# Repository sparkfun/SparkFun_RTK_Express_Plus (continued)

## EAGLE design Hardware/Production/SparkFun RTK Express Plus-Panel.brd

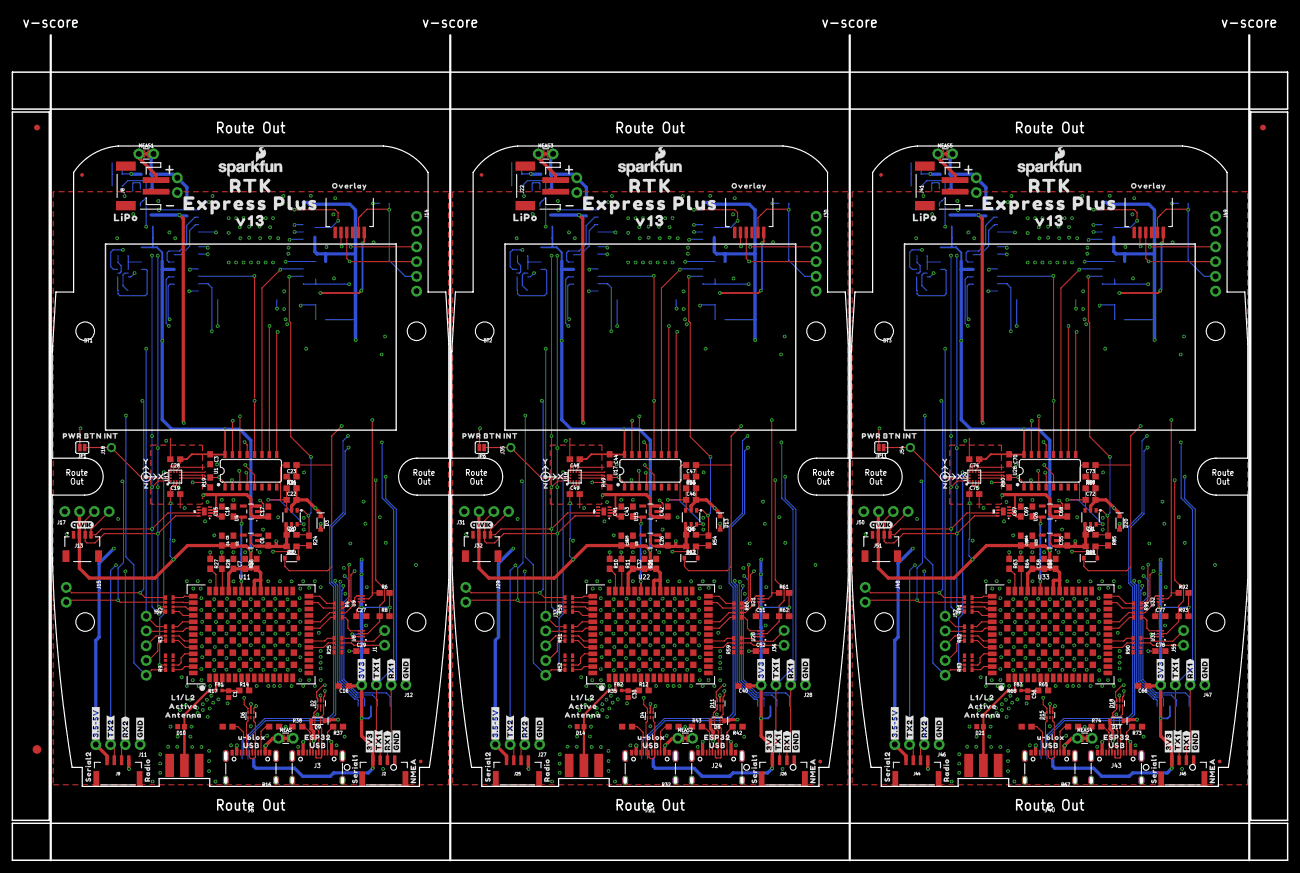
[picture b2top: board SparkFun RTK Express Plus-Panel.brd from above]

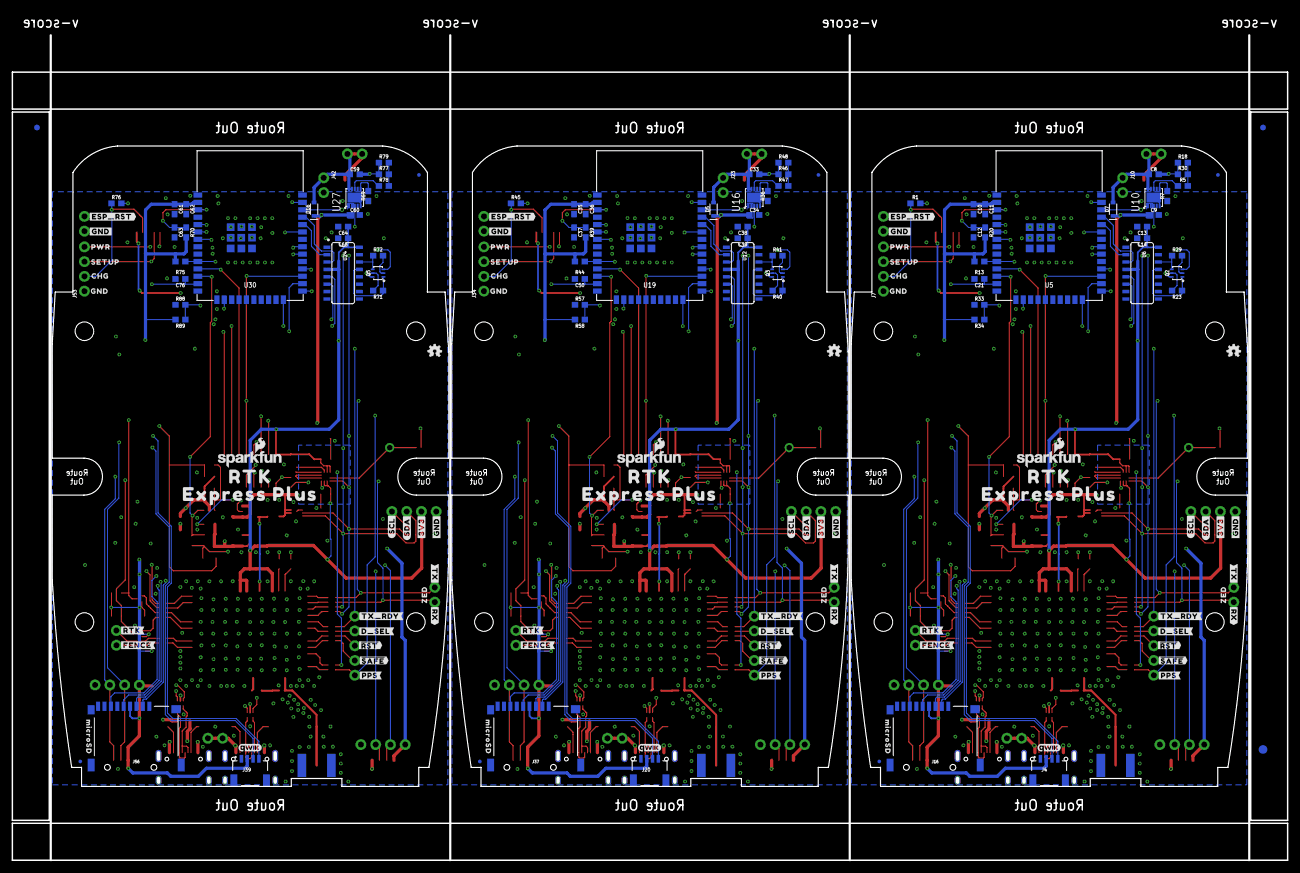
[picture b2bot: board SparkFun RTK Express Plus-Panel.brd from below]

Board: 4 copper layers, 219.3 x 141.9 mm, 510 parts (171 on the bottom side), 276 nets.

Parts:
BT1, BT2, BT3: LIPO-OUTLINE1000; LIPO-1000
C1, C30, C56: 47pF; 0402
C2, C4, C6, C17, C18, C24, C26, C31, C42, C43, C53, C55, C57, C68, C69: 1.0uF; 0603
C3, C5, C7, C11, C12, C13, C15, C16, C21, C22, C23, C25, C27, C28, C29, C32, C36, C37, C38, C40, C41, C44, C46, C47, C48, C50, C51, C52, C54, C58, C62, C63, C64, C66, C67, C70, C72, C73, C74, C76, C77, C78: 0.1uF; 0603
C8, C9, C33, C34, C59, C60: 4.7uF; 0603
C10, C14, C19, C20, C35, C39, C45, C49, C61, C65, C71, C75: 10uF; 0603
D1, D12, D19: 250mA/100V; SOD-323
D2, D4, D6, D11, D15, D18: PRTR5V0U2F; SOT886
D3, D5, D7, D8, D9, D13, D16, D17, D20: 3A/10V/280mV; SOD-323
D10, D14, D21: PESD0402-0402; 0402
E1, E2, E3: SMA; SMA-EDGE
E$1, E$2, E$3, E$4: FIDUCIAL-1X2
E$5, E$6: FIDUCIAL-1.5X3
FB1, FB2, FB3: 2.66Ω; 0402-TIGHT
J1, J10, J14, J15, J23, J29, J30, J36, J42, J48, J49, J55: 1X02_NO_SILK
J2, J9, J25, J26, J44, J45: JST-4-SMD-1.25MM-LOCKING
J3, J5, J21, J24, J40, J43: USB Female Type C Connector; USB-C-16P_4LAYER-PADS
J4, J20, J39: External; JST04_1MM_RA
J6, J33, J52: 1X05_NO_SILK
J7, J11, J12, J27, J28, J34, J46, J47, J53: 1X04_NO_SILK
J8, J22, J41: JST-2-SMD
J13, J32, J51: Internal; JST04_1MM_RA
J16, J37, J56: MICRO-SD-PUSH-PUSH-EXT-PIN; MICROSD-EXTERNALPIN
J17, J31, J50: Qwiic Right Angle; 1X04_NO_SILK
J18, J35, J54: 1X01_NO_SILK
J19, J38, J57: FPC_6_1MM-LIF
JP1, JP6, JP11: JUMPER-SMT_2_NO_SILK; SMT-JUMPER_2_NO_SILK
JP2, JP3, JP4, JP5, JP7, JP8, JP9, JP10, JP21, JP61, JP71, JP81: FIDUCIALUFIDUCIAL; FIDUCIAL-MICRO
LOGO1, LOGO4, LOGO7: OSHW-LOGOMINI; OSHW-LOGO-MINI
LOGO2, LOGO3, LOGO5, LOGO6, LOGO8, LOGO9: SFE_LOGO_NAME_FLAME.1_INCH; SFE_LOGO_NAME_FLAME_.1
MEAS, MEAS1, MEAS2, MEAS3, MEAS4, MEAS5: JUMPER-COMBO_2_NC_TRACE; COMBO-JUMPER_2_NC_TRACE
Q1, Q4, Q6: SIL2308-TP; SOT26
Q2, Q3, Q5: MBT3904DW1T1; SC70-6
R1, R45, R76: 470; 0603
R2, R3, R4, R9, R25, R50, R51, R52, R59, R60, R81, R82, R83, R90, R91: 33; 1206_RA
R5, R47, R78: 0; 0603
R6, R8, R18, R23, R29, R31, R33, R40, R41, R48, R56, R57, R61, R62, R71, R72, R79, R87, R88, R92, R93: 10k; 0603
R7, R19, R36, R49, R69, R80: 1k; 0603
R10, R11, R27, R28, R63, R64: 27; 0603
R12, R14, R65: 10; 0603
R13, R15, R20, R21, R22, R26, R39, R44, R53, R55, R66, R70, R75, R84, R86: 100k; 0603
R16, R17, R32, R35, R37, R38, R42, R43, R67, R68, R73, R74: 5.1k; 0603
R24, R54, R85: 300k; 0603
R30, R46, R77: 150k; 0603
R34, R58, R89: 3.3k; 0603
U1, U17, U28: 74HC4052D; SO16
U2, U3, U23: AP2112K-3.3; SOT23-5
U4, U15, U26: STLQ015-3.3V; SOT23-5
U5, U19, U30: ESP-WROOM-3232D; ESP-WROOM-32D
U6, U12, U24: CH340C; SO016
U7, U14, U25: MAX17048; DFN-8
U8, U9, U20, U21, U31, U32: NC7SZ14-D; SIP6
U10, U16, U27: MCP73833; DFN-10
U11, U22, U33: U-BLOX_ZED_F9R; UBLOX_ZED_F9R
U13, U18, U29: LIS2DH12; LGA-12-LISDH12
U$1, U$118, U$177: V130
U$2, U$30, U$93, U$101, U$119, U$160: QWIIC_4MM
U$3, U$102, U$161: #TX_RDY#0
U$4, U$110, U$169: INT0
U$5, U$47, U$54, U$79, U$131, U$146: #3V3#0
U$6, U$113, U$172: L1#L20
U$7, U$74, U$94, U$95, U$153, U$154: RTK0
U$8, U$112, U$171: OVERLAY0
U$9, U$111, U$170: PWR_BTN1
U$10, U$18, U$120: #RTK#1
U$11, U$71, U$140: #PPS#0
U$12, U$22, U$116, U$117, U$175, U$176: EXPRESS_PLUS0
U$13, U$114, U$173: ACTIVE1
U$14, U$73, U$141: #RX#2
U$15, U$115, U$174: ANTENNA2
U$16, U$75, U$142: ZED0
U$17, U$63, U$137: ##SAFE##5
U$19, U$26, U$121: 1553DBK-ENCLOSURE
U$20, U$27, U$122: LIPO0
U$21, U$35, U$123: U#BLOX0
U$23, U$69, U$139: #3#5#5V#0
U$24, U$107, U$166: X0
U$25, U$36, U$66, U$77, U$124, U$144: USB1
U$28, U$62, U$136: ##RST##4
U$29, U$37, U$126: SERIAL10
U$31, U$43, U$125: SERIAL20
U$32, U$64, U$138: #FENCE#3
U$33, U$103, U$162: CHG2
U$34, U$104, U$163: GND3
U$38, U$48, U$57, U$58, U$82, U$89, U$132, U$133, U$149: #GND#0
U$39, U$44, U$127: #RX2#2
U$40, U$51, U$128: #TX2#1
U$41, U$105, U$164: PWR0
U$42, U$106, U$165: SETUP1
U$45, U$52, U$68, U$81, U$129, U$148: #RX1#2
U$46, U$53, U$65, U$80, U$130, U$147: #TX1#1
U$49, U$59, U$134: NMEA1
U$50, U$61, U$135: RADIO0
U$55, U$108, U$167: Y1
U$56, U$109, U$168: Z2
U$60, U$92, U$152: #ESP_RST#0
U$67, U$78, U$145: ESP320
U$70, U$96, U$155: #GND#2
U$72, U$76, U$143: #TX#1
U$83, U$90, U$150: MICROSD0
U$84, U$91, U$151: #GND#1
U$85, U$97, U$156: #3V3#2
U$86, U$98, U$157: #SCL#1
U$87, U$99, U$158: #SDA#0
U$88, U$100, U$159: #D_SEL#0

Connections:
3.3V: C2.1, C3.1, C4.1, C5.2, C7.2, C10.1, C11.1, C13.1, C14.1, C16.1, C19.1, C27.1, C28.1, C29.1, J2.1, J4.2, J12.4, J13.2, J16.4, J17.2, R6.2, R8.2, R13.2, R15.2, R20.2, R34.2, U1.16, U2.5, U5.2, U6.4, U6.16, U8.P6, U9.P6, U11.P33, U11.P34, U11.P38, U13.2, U13.3, U13.9, U13.10
3.3V1: C24.1, C25.2, C31.1, C32.2, C35.1, C36.1, C38.1, C39.1, C40.1, C44.1, C48.1, C49.1, C51.1, C52.1, J20.2, J26.1, J28.4, J31.2, J32.2, J37.4, R21.2, R39.2, R44.2, R58.2, R61.2, R62.2, U3.5, U12.4, U12.16, U17.16, U18.2, U18.3, U18.9, U18.10, U19.2, U20.P6, U21.P6, U22.P33, U22.P34, U22.P38
3.3V2: C53.1, C54.2, C57.1, C58.2, C61.1, C62.1, C64.1, C65.1, C66.1, C70.1, C74.1, C75.1, C77.1, C78.1, J39.2, J45.1, J47.4, J50.2, J51.2, J56.4, R66.2, R70.2, R75.2, R89.2, R92.2, R93.2, U23.5, U24.4, U24.16, U28.16, U29.2, U29.3, U29.9, U29.10, U30.2, U31.P6, U32.P6, U33.P33, U33.P34, U33.P38
ANT_VCC: C1.1, FB1.2, R14.1
ANT_VCC1: C30.1, FB2.2, R12.1
ANT_VCC2: C56.1, FB3.2, R65.1
CC1: J5.A5, R17.2
CC2: J5.B5, R16.2
CC3: J3.B5, R37.2
CC4: J3.A5, R38.2
CC5: J21.A5, R35.2
CC6: J21.B5, R32.2
CC7: J24.B5, R42.2
CC8: J24.A5, R43.2
CC9: J40.A5, R68.2
CC10: J40.B5, R67.2
CC11: J43.B5, R73.2
CC12: J43.A5, R74.2
CHG_LED: R1.2, U10.3
CHG_LED1: R45.2, U16.3
CHG_LED2: R76.2, U27.3
CHG_LED_RES: J7.2, J19.2, R1.1
CHG_LED_RES1: J34.2, J38.2, R45.1
CHG_LED_RES2: J53.2, J57.2, R76.1
CHG_THERM1: R5.2, R18.2, R30.2
CHG_THERM2: R46.2, R47.2, R48.2
CHG_THERM3: R77.2, R78.2, R79.2
D+: D6.4, R27.1
D+1: D2.4, U6.5
D+2: D4.4, R10.1
D+3: D11.4, U12.5
D+4: D15.4, R63.1
D+5: D18.4, U24.5
D-: D6.6, R28.1
D-1: D2.6, U6.6
D-2: D4.6, R11.1
D-3: D11.6, U12.6
D-4: D15.6, R64.1
D-5: D18.6, U24.6
ESP32_!DTR: Q2.1, R23.1, U6.13
ESP32_!DTR1: Q3.1, R40.1, U12.13
ESP32_!DTR2: Q5.1, R71.1, U24.13
ESP32_!RTS: Q2.4, R29.1, U6.14
ESP32_!RTS1: Q3.4, R41.1, U12.14
ESP32_!RTS2: Q5.4, R72.1, U24.14
ESP32_EN: C12.1, J14.1, Q2.3, R20.1, U5.3
ESP32_EN1: C37.1, J30.1, Q3.3, R39.1, U19.3
ESP32_EN2: C63.1, J49.1, Q5.3, R70.1, U30.3
ESP32_RXI: U5.34, U6.2
ESP32_RXI1: U12.2, U19.34
ESP32_RXI2: U24.2, U30.34
ESP32_TXO: U5.35, U6.3
ESP32_TXO1: U12.3, U19.35
ESP32_TXO2: U24.3, U30.35
ESP_0/BOOT: Q2.6, U5.25
ESP_0/BOOT1: Q3.6, U19.25
ESP_0/BOOT2: Q5.6, U30.25
ESP_2/MUX_A: U1.10, U5.24
ESP_2/MUX_A1: U17.10, U19.24
ESP_2/MUX_A2: U28.10, U30.24
ESP_4/ACCEL_INT: J18.1, JP1.1, U13.12
ESP_4/ACCEL_INT1: J35.1, JP6.1, U18.12
ESP_4/ACCEL_INT2: J54.1, JP11.1, U29.12
ESP_4/MUX_B: U1.9, U5.26
ESP_4/MUX_B1: U17.9, U19.26
ESP_4/MUX_B2: U28.9, U30.26
ESP_13/POWER_CTRL: D1.A, R22.1, R24.2, U5.16
ESP_13/POWER_CTRL1: D12.A, R53.1, R54.2, U19.16
ESP_13/POWER_CTRL2: D19.A, R84.1, R85.2, U30.16
ESP_14/SETUP_BUTTON: C21.1, J7.3, J19.4, U5.13
ESP_14/SETUP_BUTTON1: C50.1, J34.3, J38.4, U19.13
ESP_14/SETUP_BUTTON2: C76.1, J53.3, J57.4, U30.13
ESP_18/SCK: J16.5, U5.30
ESP_18/SCK1: J37.5, U19.30
ESP_18/SCK2: J56.5, U30.30
ESP_19/POCI: J16.7, U5.31
ESP_19/POCI1: J37.7, U19.31
ESP_19/POCI2: J56.7, U30.31
ESP_21/SDA: J4.3, J13.3, J17.3, R2.P7, U5.33, U7.8, U13.4
ESP_21/SDA1: J20.3, J31.3, J32.3, R50.P7, U14.8, U18.4, U19.33
ESP_21/SDA2: J39.3, J50.3, J51.3, R81.P7, U25.8, U29.4, U30.33
ESP_22/SCL: J4.4, J13.4, J17.4, R2.P8, U5.36, U7.7, U13.1
ESP_22/SCL1: J20.4, J31.4, J32.4, R50.P8, U14.7, U18.1, U19.36
ESP_22/SCL2: J39.4, J50.4, J51.4, R81.P8, U25.7, U29.1, U30.36
ESP_23/PICO: J16.3, U5.37
ESP_23/PICO1: J37.3, U19.37
ESP_23/PICO2: J56.3, U30.37
ESP_25/SD_!CS!: J16.2, R13.1, U5.10
ESP_25/SD_!CS!1: J37.2, R44.1, U19.10
ESP_25/SD_!CS!2: J56.2, R75.1, U30.10
ESP_26/DAC1: U17.11, U19.11
ESP_26/DAC2: U1.11, U5.11
ESP_26/DAC3: U28.11, U30.11
ESP_26/ZED_TX_READY_LV: R3.P4, U11.P46
ESP_26/ZED_TX_READY_LV1: R51.P4, U22.P46
ESP_26/ZED_TX_READY_LV2: R82.P4, U33.P46
ESP_27/FAST_OFF: C20.2, Q1.G1, R24.1, U5.12
ESP_27/FAST_OFF1: C45.2, Q4.G1, R54.1, U19.12
ESP_27/FAST_OFF2: C71.2, Q6.G1, R85.1, U30.12
ESP_D1+: D2.3, J3.A6, J3.B6
ESP_D1+1: D11.3, J24.A6, J24.B6
ESP_D1+2: D18.3, J43.A6, J43.B6
ESP_D1-: D2.1, J3.A7, J3.B7
ESP_D1-1: D11.1, J24.A7, J24.B7
ESP_D1-2: D18.1, J43.A7, J43.B7
ESP_I16/ZED-TXO1: J15.1, R2.P5, U1.12, U5.27
ESP_I16/ZED-TXO2: J29.1, R50.P5, U17.12, U19.27
ESP_I16/ZED-TXO3: J48.1, R81.P5, U28.12, U30.27
ESP_I34/ZED_TX_READY: J6.1, R3.P5, U5.6
ESP_I34/ZED_TX_READY1: J33.1, R51.P5, U19.6
ESP_I34/ZED_TX_READY2: J52.1, R82.P5, U30.6
ESP_I35/DEVICE_SENSE: R33.2, R34.1, U5.7
ESP_I35/DEVICE_SENSE1: R57.2, R58.1, U19.7
ESP_I35/DEVICE_SENSE2: R88.2, R89.1, U30.7
ESP_I39/ADC1: U17.4, U19.5
ESP_I39/ADC2: U28.4, U30.5
ESP_I39/ADC39: U1.4, U5.5
ESP_O17/ZED-RXI1: J15.2, R2.P6, R19.2, U1.1
ESP_O17/ZED-RXI2: J29.2, R49.2, R50.P6, U17.1
ESP_O17/ZED-RXI3: J48.2, R80.2, R81.P6, U28.1
EXTERNAL_DATA_IN: J2.3, J12.2, U1.3
EXTERNAL_DATA_IN1: J26.3, J28.2, U17.3
EXTERNAL_DATA_IN2: J45.3, J47.2, U28.3
EXTERNAL_DATA_OUT: J2.2, J12.3, U1.13
EXTERNAL_DATA_OUT1: J26.2, J28.3, U17.13
EXTERNAL_DATA_OUT2: J45.2, J47.3, U28.13
EXTINT_LV: R9.P2, U11.P51
EXTINT_LV1: R52.P2, U22.P51
EXTINT_LV2: R83.P2, U33.P51
EXT_DIR: R6.1, U1.15, U9.P2
EXT_DIR1: R61.1, U17.15, U21.P2
EXT_DIR2: R92.1, U28.15, U32.P2
EXT_WT: R8.1, U1.2, U8.P2
EXT_WT1: R62.1, U17.2, U20.P2
EXT_WT2: R93.1, U28.2, U31.P2
FENCE_LV: R25.P6, U11.P19
FENCE_LV1: R59.P6, U22.P19
FENCE_LV2: R90.P6, U33.P19
GND: C1.2, C2.2, C3.2, C4.2, C5.1, C6.2, C7.1, C8.2, C9.2, C10.2, C11.2, C12.2, C13.2, C14.2, C15.2, C16.2, C17.2, C18.2, C19.2, C21.2, C27.2, C28.2, C29.2, D2.2, D6.2, D10.2, E1.GND@0, E1.GND@1, E1.GND@2, E1.GND@3, J2.4, J3.GND, J3.GND2, J3.SHLD1, J3.SHLD2, J3.SHLD3, J3.SHLD4, J4.1, J5.GND, J5.GND2, J5.SHLD1, J5.SHLD2, J5.SHLD3, J5.SHLD4, J7.1, J8.1, J9.4, J10.2, J11.1, J12.1, J13.1, J14.2, J16.6, J16.10, J16.11, J16.12, J16.13, J17.1, J19.6, Q1.S1, R7.1, R15.1, R16.1, R17.1, R18.1, R30.1, R33.1, R37.1, R38.1, U1.6, U1.7, U1.8, U2.2, U4.2, U5.1, U5.15, U5.38, U5.GND, U5.GNDT1, U5.GNDT2, U5.GNDT3, U5.GNDT4, U5.GNDT5, U5.GNDT6, U5.GNDT7, U5.GNDT8, U6.1, U7.1, U7.4, U7.6, U7.9, U8.P3, U9.P3, U10.5, U10.11, U11.G1, U11.G2, U11.G3, U11.G4, U11.G5, U11.G6, U11.G7, U11.G8, U11.G9, U11.G10, U11.G11, U11.G12, U11.G13, U11.G14, U11.G15, U11.G16, U11.G17, U11.G18, U11.G19, U11.G20, U11.G21, U11.G22, U11.G23, U11.G24, U11.G25, U11.G26, U11.G27, U11.G28, U11.G29, U11.G30, U11.G31, U11.G32, U11.G33, U11.G34, U11.G35, U11.G36, U11.G37, U11.G38, U11.G39, U11.G40, U11.G41, U11.G42, U11.G43, U11.G44, U11.G45, U11.G46, U11.G47, U11.G48, U11.P1, U11.P3, U11.P12, U11.P14, U11.P32, U11.P37, U11.P41, U11.P48, U13.5, U13.6, U13.7, U13.8
GND1: C24.2, C25.1, C26.2, C30.2, C31.2, C32.1, C33.2, C34.2, C35.2, C36.2, C37.2, C38.2, C39.2, C40.2, C41.2, C42.2, C43.2, C44.2, C48.2, C49.2, C50.2, C51.2, C52.2, D4.2, D11.2, D14.2, E2.GND@0, E2.GND@1, E2.GND@2, E2.GND@3, J20.1, J21.GND, J21.GND2, J21.SHLD1, J21.SHLD2, J21.SHLD3, J21.SHLD4, J22.1, J23.2, J24.GND, J24.GND2, J24.SHLD1, J24.SHLD2, J24.SHLD3, J24.SHLD4, J25.4, J26.4, J27.1, J28.1, J30.2, J31.1, J32.1, J34.1, J37.6, J37.10, J37.11, J37.12, J37.13, J38.6, Q4.S1, R21.1, R32.1, R35.1, R36.1, R42.1, R43.1, R46.1, R48.1, R57.1, U3.2, U12.1, U14.1, U14.4, U14.6, U14.9, U15.2, U16.5, U16.11, U17.6, U17.7, U17.8, U18.5, U18.6, U18.7, U18.8, U19.1, U19.15, U19.38, U19.GND, U19.GNDT1, U19.GNDT2, U19.GNDT3, U19.GNDT4, U19.GNDT5, U19.GNDT6, U19.GNDT7, U19.GNDT8, U20.P3, U21.P3, U22.G1, U22.G2, U22.G3, U22.G4, U22.G5, U22.G6, U22.G7, U22.G8, U22.G9, U22.G10, U22.G11, U22.G12, U22.G13, U22.G14, U22.G15, U22.G16, U22.G17, U22.G18, U22.G19, U22.G20, U22.G21, U22.G22, U22.G23, U22.G24, U22.G25, U22.G26, U22.G27, U22.G28, U22.G29, U22.G30, U22.G31, U22.G32, U22.G33, U22.G34, U22.G35, U22.G36, U22.G37, U22.G38, U22.G39, U22.G40, U22.G41, U22.G42, U22.G43, U22.G44, U22.G45, U22.G46, U22.G47, U22.G48, U22.P1, U22.P3, U22.P12, U22.P14, U22.P32, U22.P37, U22.P41, U22.P48
GND2: C53.2, C54.1, C55.2, C56.2, C57.2, C58.1, C59.2, C60.2, C61.2, C62.2, C63.2, C64.2, C65.2, C66.2, C67.2, C68.2, C69.2, C70.2, C74.2, C75.2, C76.2, C77.2, C78.2, D15.2, D18.2, D21.2, E3.GND@0, E3.GND@1, E3.GND@2, E3.GND@3, J39.1, J40.GND, J40.GND2, J40.SHLD1, J40.SHLD2, J40.SHLD3, J40.SHLD4, J41.1, J42.2, J43.GND, J43.GND2, J43.SHLD1, J43.SHLD2, J43.SHLD3, J43.SHLD4, J44.4, J45.4, J46.1, J47.1, J49.2, J50.1, J51.1, J53.1, J56.6, J56.10, J56.11, J56.12, J56.13, J57.6, Q6.S1, R66.1, R67.1, R68.1, R69.1, R73.1, R74.1, R77.1, R79.1, R88.1, U23.2, U24.1, U25.1, U25.4, U25.6, U25.9, U26.2, U27.5, U27.11, U28.6, U28.7, U28.8, U29.5, U29.6, U29.7, U29.8, U30.1, U30.15, U30.38, U30.GND, U30.GNDT1, U30.GNDT2, U30.GNDT3, U30.GNDT4, U30.GNDT5, U30.GNDT6, U30.GNDT7, U30.GNDT8, U31.P3, U32.P3, U33.G1, U33.G2, U33.G3, U33.G4, U33.G5, U33.G6, U33.G7, U33.G8, U33.G9, U33.G10, U33.G11, U33.G12, U33.G13, U33.G14, U33.G15, U33.G16, U33.G17, U33.G18, U33.G19, U33.G20, U33.G21, U33.G22, U33.G23, U33.G24, U33.G25, U33.G26, U33.G27, U33.G28, U33.G29, U33.G30, U33.G31, U33.G32, U33.G33, U33.G34, U33.G35, U33.G36, U33.G37, U33.G38, U33.G39, U33.G40, U33.G41, U33.G42, U33.G43, U33.G44, U33.G45, U33.G46, U33.G47, U33.G48, U33.P1, U33.P3, U33.P12, U33.P14, U33.P32, U33.P37, U33.P41, U33.P48
GPS_ANT1: D10.1, E1.SIG, FB1.1, U11.P2
GPS_ANT2: D14.1, E2.SIG, FB2.1, U22.P2
GPS_ANT3: D21.1, E3.SIG, FB3.1, U33.P2
LIPO_RAW: J8.2, MEAS1.1, MEAS1.3
LIPO_RAW1: J22.2, MEAS3.1, MEAS3.3
LIPO_RAW2: J41.2, MEAS5.1, MEAS5.3
unnamed: R10.2, U22.P40
unnamed: R4.P4, U11.P22
unnamed: R4.P3, U11.P23
unnamed: J5.VBUS1, J5.VBUS2, MEAS.1, MEAS.3
unnamed: R5.1, U10.8
unnamed: R19.1, U5.28
unnamed: R11.2, U22.P39
unnamed: R12.2, U22.P7
unnamed: Q3.5, R40.2
unnamed: Q3.2, R41.2
unnamed: R27.2, U11.P40
unnamed: R28.2, U11.P39
unnamed: R14.2, U11.P7
unnamed: D8.A, J24.VBUS1, J24.VBUS2
unnamed: C22.1, C23.2, Q1.D1, Q1.G2, R26.1
unnamed: J21.VBUS1, J21.VBUS2, MEAS2.1, MEAS2.3
unnamed: R47.1, U16.8
unnamed: R49.1, U19.28
unnamed: C46.1, C47.2, Q4.D1, Q4.G2, R55.1
unnamed: R60.P4, U22.P22
unnamed: R60.P3, U22.P23
unnamed: R63.2, U33.P40
unnamed: R64.2, U33.P39
unnamed: Q2.5, R23.2
unnamed: Q2.2, R29.2
unnamed: R65.2, U33.P7
unnamed: Q5.5, R71.2
unnamed: Q5.2, R72.2
unnamed: D17.A, J43.VBUS1, J43.VBUS2
unnamed: J40.VBUS1, J40.VBUS2, MEAS4.1, MEAS4.3
unnamed: R78.1, U27.8
unnamed: D9.A, J3.VBUS1, J3.VBUS2
unnamed: R80.1, U30.28
unnamed: C72.1, C73.2, Q6.D1, Q6.G2, R86.1
unnamed: R91.P4, U33.P22
unnamed: R91.P3, U33.P23
POWER_BTN: C23.1, D1.C, J7.4, J19.5, JP1.2, R31.1
POWER_BTN1: C47.1, D12.C, J34.4, J38.5, JP6.2, R56.1
POWER_BTN2: C73.1, D19.C, J53.4, J57.5, JP11.2, R87.1
PPS_LV: R9.P1, U11.P53
PPS_LV1: R52.P1, U22.P53
PPS_LV2: R83.P1, U33.P53
PROG1: R7.2, U10.6
PROG2: R36.2, U16.6
PROG3: R69.2, U27.6
RTK_STAT_LV: R25.P5, U11.P20
RTK_STAT_LV1: R59.P5, U22.P20
RTK_STAT_LV2: R90.P5, U33.P20
RX2_LV: R4.P2, U11.P26
RX2_LV1: R60.P2, U22.P26
RX2_LV2: R91.P2, U33.P26
RXLV: R2.P3, U11.P43
RXLV1: R50.P3, U22.P43
RXLV2: R81.P3, U33.P43
SCL_LV: R2.P1, U11.P45
SCL_LV1: R50.P1, U22.P45
SCL_LV2: R81.P1, U33.P45
SDA_LV: R2.P2, U11.P44
SDA_LV1: R50.P2, U22.P44
SDA_LV2: R81.P2, U33.P44
TX2_LV: R4.P1, U11.P27
TX2_LV1: R60.P1, U22.P27
TX2_LV2: R91.P1, U33.P27
TXLV: R2.P4, U11.P42
TXLV1: R50.P4, U22.P42
TXLV2: R81.P4, U33.P42
UNP_D+: D6.3, J5.A6, J5.B6
UNP_D+1: D4.3, J21.A6, J21.B6
UNP_D+2: D15.3, J40.A6, J40.B6
UNP_D-: D6.1, J5.A7, J5.B7
UNP_D-1: D4.1, J21.A7, J21.B7
UNP_D-2: D15.1, J40.A7, J40.B7
VOUT: C6.1, C20.1, J9.1, J11.4, Q1.D2, R22.2, U2.1, U2.3
VOUT1: C26.1, C45.1, J25.1, J27.4, Q4.D2, R53.2, U3.1, U3.3
VOUT2: C55.1, C71.1, J44.1, J46.4, Q6.D2, R84.2, U23.1, U23.3
V_BATT: C8.1, C15.1, C17.1, D7.A, J10.1, MEAS1.2, MEAS1.4, U4.1, U4.3, U7.2, U7.3, U10.9, U10.10
V_BATT1: C33.1, C41.1, C42.1, D5.A, J23.1, MEAS3.2, MEAS3.4, U14.2, U14.3, U15.1, U15.3, U16.9, U16.10
V_BATT2: C59.1, C67.1, C68.1, D16.A, J42.1, MEAS5.2, MEAS5.4, U25.2, U25.3, U26.1, U26.3, U27.9, U27.10
V_BKCP: C18.1, U4.5, U11.P36
V_BKCP1: C43.1, U15.5, U22.P36
V_BKCP2: C69.1, U26.5, U33.P36
V_RAW: C9.1, C22.2, D3.C, D7.C, Q1.S2, R26.2, R31.2, U10.1, U10.2
V_RAW1: C34.1, C46.2, D5.C, D13.C, Q4.S2, R55.2, R56.2, U16.1, U16.2
V_RAW2: C60.1, C72.2, D16.C, D20.C, Q6.S2, R86.2, R87.2, U27.1, U27.2
V_USB: D2.5, D3.A, D6.5, D9.C, J19.1, MEAS.2, MEAS.4
V_USB1: D4.5, D8.C, D11.5, D13.A, J38.1, MEAS2.2, MEAS2.4
V_USB2: D15.5, D17.C, D18.5, D20.A, J57.1, MEAS4.2, MEAS4.4
ZED-RXI1: J25.3, J27.2, R60.P7
ZED-RXI2: J9.3, J11.2, R4.P7
ZED-RXI3: J44.3, J46.2, R91.P7
ZED-TXO1: J25.2, J27.3, R60.P8
ZED-TXO2: J9.2, J11.3, R4.P8
ZED-TXO3: J44.2, J46.3, R91.P8
ZED_!RESET!: J6.3, R3.P7
ZED_!RESET!1: J33.3, R51.P7
ZED_!RESET!2: J52.3, R82.P7
ZED_!RESET!_LV: R3.P2, U11.P49
ZED_!RESET!_LV1: R51.P2, U22.P49
ZED_!RESET!_LV2: R82.P2, U33.P49
ZED_!SAFE!: J6.4, R3.P8
ZED_!SAFE!1: J33.4, R51.P8
ZED_!SAFE!2: J52.4, R82.P8
ZED_!SAFE!_LV: R3.P1, U11.P50
ZED_!SAFE!_LV1: R51.P1, U22.P50
ZED_!SAFE!_LV2: R82.P1, U33.P50
ZED_DIR: R4.P6, U9.P4
ZED_DIR1: R60.P6, U21.P4
ZED_DIR2: R91.P6, U32.P4
ZED_D_SEL: J6.2, R3.P6
ZED_D_SEL1: J33.2, R51.P6
ZED_D_SEL2: J52.2, R82.P6
ZED_D_SEL_LV: R3.P3, U11.P47
ZED_D_SEL_LV1: R51.P3, U22.P47
ZED_D_SEL_LV2: R82.P3, U33.P47
ZED_EXTINT: R9.P7, U1.5
ZED_EXTINT1: R52.P7, U17.5
ZED_EXTINT2: R83.P7, U28.5
ZED_FENCE_STAT: J1.1, R25.P3
ZED_FENCE_STAT1: J36.1, R59.P3
ZED_FENCE_STAT2: J55.1, R90.P3
ZED_PPS_STAT: J6.5, R9.P8, U1.14
ZED_PPS_STAT1: J33.5, R52.P8, U17.14
ZED_PPS_STAT2: J52.5, R83.P8, U28.14
ZED_RTK_STAT: J1.2, R25.P4
ZED_RTK_STAT1: J36.2, R59.P4
ZED_RTK_STAT2: J55.2, R90.P4
ZED_WT: R4.P5, U8.P4
ZED_WT1: R60.P5, U20.P4
ZED_WT2: R91.P5, U31.P4

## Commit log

2021-07-09 Remove post mux opto isolation. Create v10 panel.
2021-09-20 Add docs
2021-09-20 Add rover with fusion graphic
2021-09-20 File rename
2021-09-20 Update overlay graphics to Plus
2021-09-20 Create panel files for v11 PCB
2021-09-29 Updating readme. Update version to v11 on schematic.
2022-02-03 Update issue templates
2022-02-24 v12 PCB - remove ground plane from accelerometer. Remove old files.
2022-03-30 Add route out note
2022-05-19 v13 PCB - LIF connector, accel ground plane, ESP32 FP.
    * Removed ground plane from around the accel to aid in reflow and rework
    * Route out text in screw areas
    * New 6 pin overlay connector
    * ENIG finish
    * Full ESP32 FP
2022-05-19 v13 - Change to LIF overlay connector. Change ESP32 FP. Pull ground from accel.
2022-05-19 Add ID Panel
2024-12-20 Add enclosure 3D file
